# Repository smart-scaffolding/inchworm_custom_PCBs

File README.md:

# inchworm_custom_PCBs
Contains custom PCBs for the robotic inchworm version one and two. The Kicad software was used to make these PCBs.

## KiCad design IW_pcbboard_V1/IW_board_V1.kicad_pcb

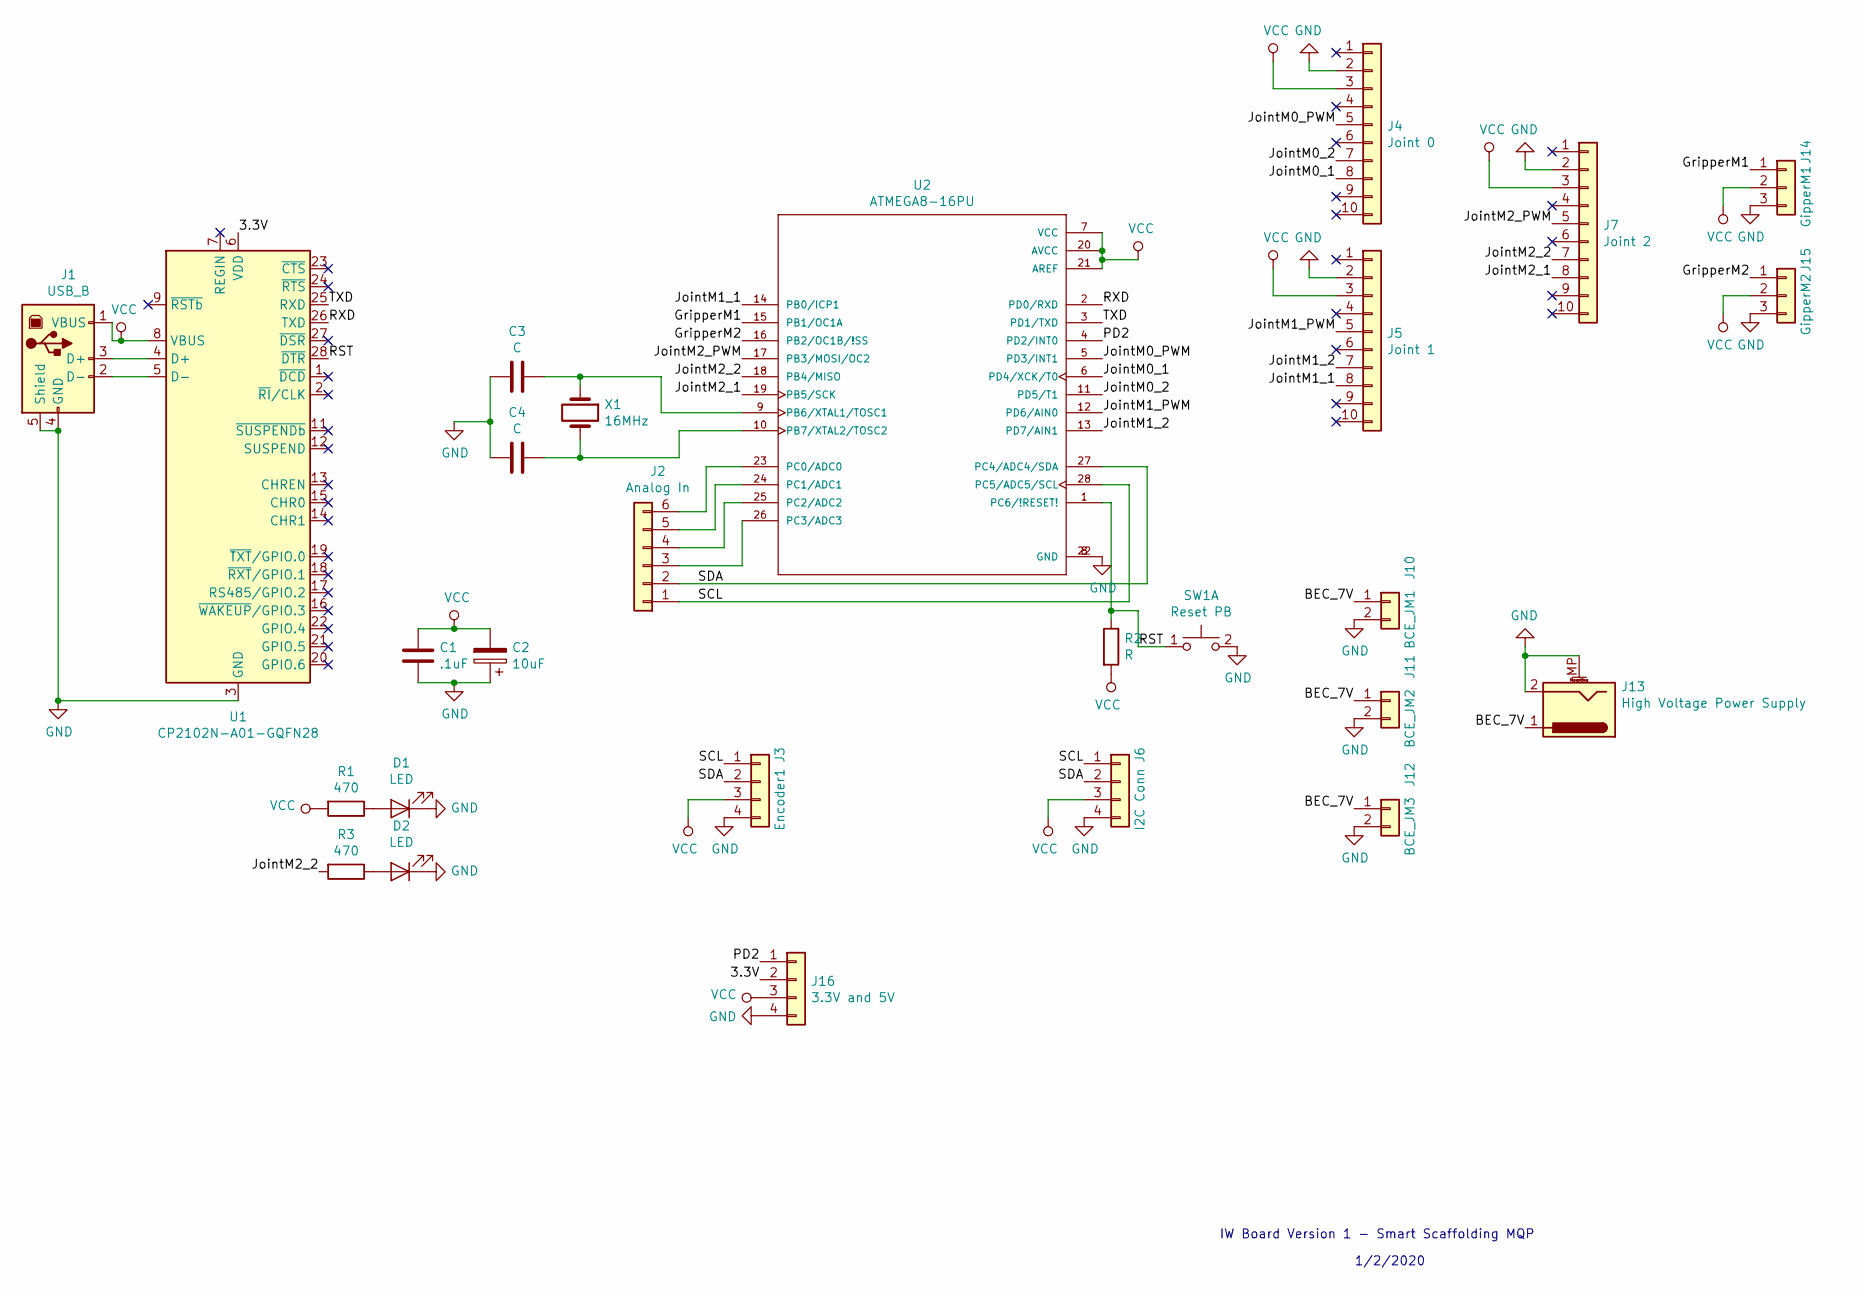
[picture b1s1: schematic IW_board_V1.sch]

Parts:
C1: .1uF; C_0402_1005Metric
C2: 10uF; C_0603_1608Metric
C3, C4: C; C_0402_1005Metric
D1, D2: LED; LED_0805_2012Metric_Pad1.15x1.40mm_HandSolder
J1: USB_B; USB_B_OST_USB-B1HSxx_Horizontal
J2: Analog In; PinSocket_1x06_P2.54mm_Vertical
J3: Encoder1; PinSocket_1x04_P2.54mm_Vertical
J4: Joint 0; PinSocket_1x10_P2.54mm_Vertical
J5: Joint 1; PinSocket_1x10_P2.54mm_Vertical
J6: I2C Conn; PinSocket_1x04_P2.54mm_Vertical
J7: Joint 2; PinSocket_1x10_P2.54mm_Vertical
J10: BCE_JM1; PinSocket_1x02_P2.54mm_Vertical
J11: BCE_JM2; PinSocket_1x02_P2.54mm_Vertical
J12: BCE_JM3; PinSocket_1x02_P2.54mm_Vertical
J13: High Voltage Power Supply; CUI_PJ-082BH
J14: GipperM1; PinSocket_1x03_P2.54mm_Vertical
J15: GipperM2; PinSocket_1x03_P2.54mm_Vertical
J16: 3.3V and 5V; PinSocket_1x04_P2.54mm_Vertical
R1, R3: 470; R_0805_2012Metric
R2: R; R_0402_1005Metric
SW1: Reset PB; SW_PUSH_6mm
U1: CP2102N-A01-GQFN28; QFN-28-1EP_5x5mm_P0.5mm_EP3.35x3.35mm
U2: ATMEGA8-16PU; DIP793W45P254L3479H457Q28
X1: 16MHz; Crystal_HC49-4H_Vertical

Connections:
/3.3V: J16.2, U1.6 (VDD)
/BEC_7V: J10.1, J11.1, J12.1, J13.1
/GripperM1: J14.1, U2.15 (PB1/OC1A)
/GripperM2: J15.1, U2.16 (PB2/OC1B/!SS)
/JointM0_1: J4.8, U2.6 (PD4/XCK/T0)
/JointM0_2: J4.7, U2.11 (PD5/T1)
/JointM0_PWM: J4.5, U2.5 (PD3/INT1)
/JointM1_1: J5.8, U2.14 (PB0/ICP1)
/JointM1_2: J5.7, U2.13 (PD7/AIN1)
/JointM1_PWM: J5.5, U2.12 (PD6/AIN0)
/JointM2_1: J7.8, U2.19 (PB5/SCK)
/JointM2_2: J7.7, R3.2, U2.18 (PB4/MISO)
/JointM2_PWM: J7.5, U2.17 (PB3/MOSI/OC2)
/PD2: J16.1, U2.4 (PD2/INT0)
/RST: R2.1, SW1.1 (C), U1.28 (~DTR), U2.1 (PC6/!RESET!)
/RXD: U1.26 (TXD), U2.2 (PD0/RXD)
/SCL: J2.1, J3.1, J6.1, U2.28 (PC5/ADC5/SCL)
/SDA: J2.2, J3.2, J6.2, U2.27 (PC4/ADC4/SDA)
/TXD: U1.25 (RXD), U2.3 (PD1/TXD)
GND: C1.2, C2.1, C3.2, C4.2, D1.1 (K), D2.1 (K), J1.4 (GND), J1.5 (Shield), J3.4, J4.2, J5.2, J6.4, J7.2, J10.2, J11.2, J12.2, J13.2, J13.MP (MountPin), J14.3, J15.3, J16.4, SW1.2 (D), U1.3 (GND), U1.29 (GND), U2.8 (GND), U2.22 (GND)
unnamed: C3.1, U2.9 (PB6/XTAL1/TOSC1), X1.1
unnamed: C4.1, U2.10 (PB7/XTAL2/TOSC2), X1.2
unnamed: D1.2 (A), R1.1
unnamed: D2.2 (A), R3.1
unnamed: J1.2 (D-), U1.5 (D-)
unnamed: J1.3 (D+), U1.4 (D+)
unnamed: J2.3, U2.26 (PC3/ADC3)
unnamed: J2.4, U2.25 (PC2/ADC2)
unnamed: J2.5, U2.24 (PC1/ADC1)
unnamed: J2.6, U2.23 (PC0/ADC0)
VCC: C1.1, C2.2, J1.1 (VBUS), J3.3, J4.3, J5.3, J6.3, J7.3, J14.2, J15.2, J16.3, R1.2, R2.2, U1.8 (VBUS), U2.7 (VCC), U2.20 (AVCC), U2.21 (AREF)

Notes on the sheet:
IW Board Version 1 - Smart Scaffolding MQP
1/2/2020

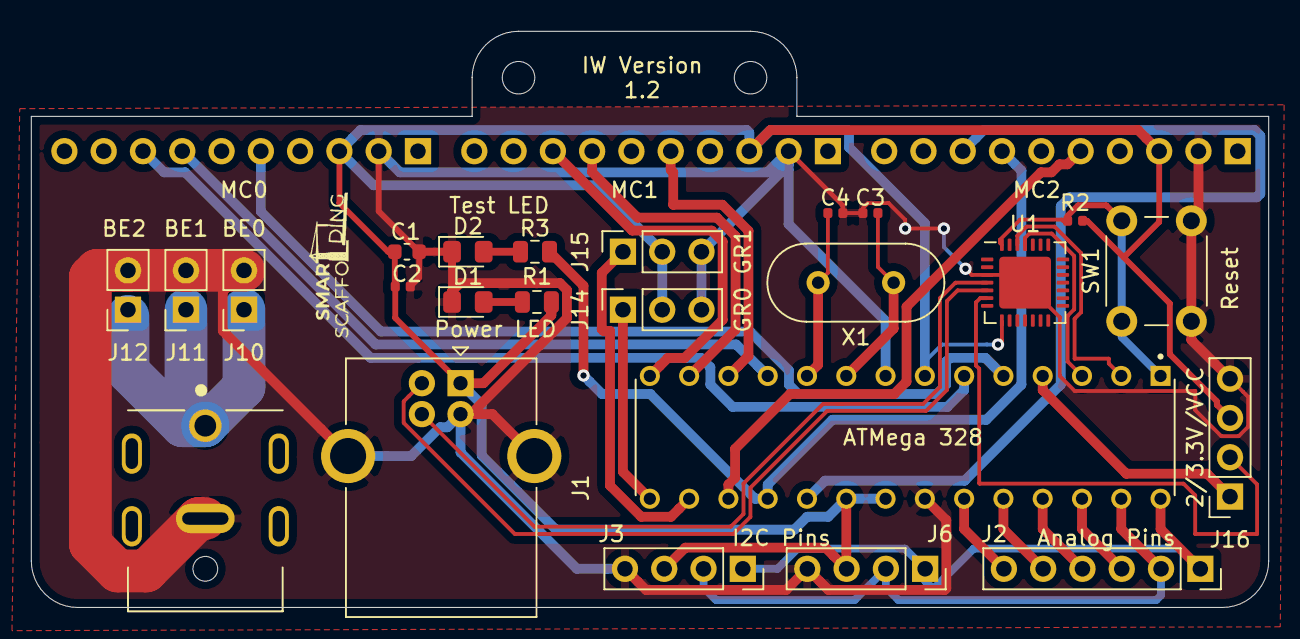
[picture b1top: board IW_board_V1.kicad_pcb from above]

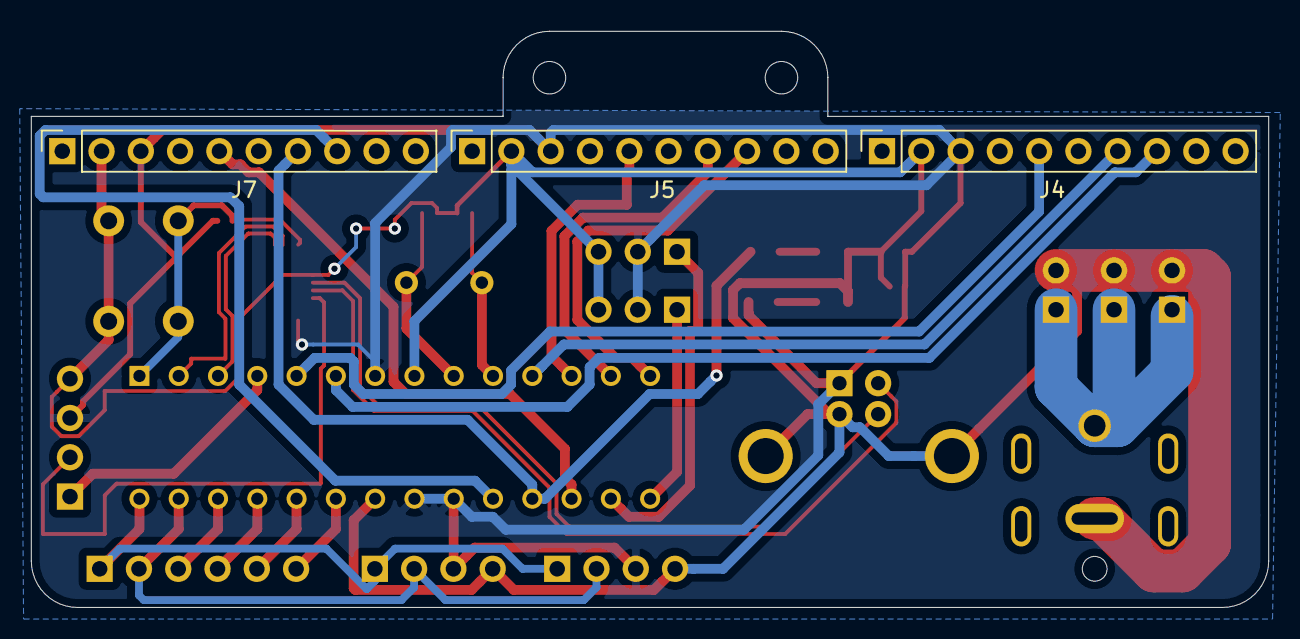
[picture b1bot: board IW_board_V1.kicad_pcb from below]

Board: 2 copper layers, 80.0 x 37.2 mm, 27 parts (3 on the bottom side), 31 nets.

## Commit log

2020-02-24 Final version of IW V1 board.
2020-02-24 added picture of board
